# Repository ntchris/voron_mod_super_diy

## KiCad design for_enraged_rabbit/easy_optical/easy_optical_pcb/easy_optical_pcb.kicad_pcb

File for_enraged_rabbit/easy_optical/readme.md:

# ERCF Easy Optical Encoder Module
For ERCF: to make it easier for everyone to use a transmissive optical sensor

in one simple sentence, a DIY friendly, a much cheaper and easier blinky sensor module for ERCF.

## What is this:

for ERCF (Enraged Rabbit Carrot Feeder Multiple Material System for Voron or alike 3D printers)
replace the original reflective optical sensor which is quite not reliable.
so mneuhaus made a transmissive optical sensor encoder called Binky, which should provide a much more reliable encoder functions/counter.
 https://github.com/mneuhaus/EnragedRabbitProject/tree/main/usermods/Binky
 
* What is a transmissive optical sensor
an optical sensor, or photo sensor, slot type, like SX1103, or ITR9608.
It has a infrared diode and a receiver, if an object blocks the infrared light, the receiver detects it and triggers/send a signal.

However, there are still some problems remains with Binky module, 
* blinky PCB is quite expensive, plus shipping (international!) and tax, I'm afraid we are looking at ~~30$ or more. 
* Also the PCB is quite difficult to make via DIY methods. 
* And some components, in my opinion, is too expensive or useless.
So I made this Easy Optical module for ERCF.
The goal is to save a ton of money not to buy binky PCB or wait for shipping, or buy some expensive and /or unncessary components. 
and we can make it using some easy home DIY methods, CNC milling or chemical etching.

## Easy Optical PCB module feature list:
* single side PCB design, reduce PCB DIY complicity
* 0.5mm thick traces and large clearance, good precision/error tolerance, so we can easily make it at home with a cheap CNC or chemical method. I made mine using a DIY CNC made by myself.
* Use a much cheaper slotted optical sensor - ITR20403, it's small enough and very cheap, about 2$ for 10pcs. 
https://everlighteurope.com/index.php?controller=attachment?id_attachment=5394 comparing with the SX1103, it's about 1$ each.
* removed a useless component small inverter, to reduce cost and efforts for making the pcb/soldering.
* using a 3mm through hole LED, it fits the rabbit eyes much better and brighter.
* Kicad 7 is used to create the schematics and PCB. full schematics/PCB project/source are provided

## Things to pay attention while making the PCB at home.
* Only front side of the PCB is needed, back side is not needed, just optional.
* for single side PCB, the 3pins connector must be soldered on the front side of the PCB, because the back side has no copper. 
* For single side PCB, the 3pins connect drill hole better be 0.8mm, so it's tight enough. If the holes are too large, the pin will be easily pulled out since the copper is not strong enough to hold it against some large pull up force.
* If don't care about flashing rabbit eyes, some components are not needed, so to make it even easier to make: R3 (D1 3mm LED, R3 1k)for LED, Q1 ( AO3402 Nchannel Mosfet), C2 (10u)
* when installing the ITR20403, the 45 degree edge is facing outside of PCB, longer pin is facing 3mm led. there are two plastic mounting pin under it, one is larger, it's closer to the 3mm led. hold it tight and close on the PCB when solder.

## Component list
* C1	1	1u	C      0805 SMD Capacitor, filtering signal.
* C2	1	10u	C      0805 SMD Capacitor, optional
* D1	1	LED	LED    3mm red LED, A on right, K on left. optional
* H1	1	MountingHole	2mm mounting hole.
* J1	1	Conn_01x03	Conn_01x03,  
* Q1	1	AO3402_N_Mosfet	, Nchannel mosfet, for red LED only, optional.
* R1    1   1K  R   0805 SMD Resistor,  for optical sensor infrared
* R3	1	1k	R   0805 SMD Resistor    Optional
* R2	1	10k	R      0805 SMD Resistor , pull up for optical sensor
* R4	1	0	R     1206 0R resistor, act as a jumper wire, if don't have it, just fly a wire.
* U1	1	ITR20403  optical sensor

## Operation theory

It couldn't be simpler and easier than this.
* When the ITR20403 sensor is power on, R1 (1K) resistor make 5V power supply to provide and reduce a suitable current for the sensor's infrared led, about (5-2)/1k = ~~3ma.
* When nothing blocking, the infrared light fire on the other side collector/emitter, so it's kind of connected, so our signal termial has about 0V, low.
* When our 3D printed gear blocking the infrared, the E/C is disconnected, so the signal point is pull high.
So our easy optical module can send low/high signal as the gear rotates, and it's super reliable, since the gear can always block the light and let the light pass.

* Optional for blinking rabbit eyes.
 N channel mosfet gate when pull high, it power on the 3mm LED.

( low or high doesn't matter in our application, as long as it can be triggered and change, it's good enough. also this is not a high speed application. )

## Encoder 3DPrint part 
The 3D pirnted part is modified based on binky's encoder however made quite a few changes as below:

### modification list:

1. larger cut for optical sensor, so it fits IT20403  ( 7mm for sensor 6.4mm width, 4.7mm for 4.2mm length.), it's slightly larger than the sx1103 (in binky pcb), but much much cheaper than SX1103. ITR20403 is only a bit wider than it (6.4mm VS 5mm).
1. larger LED hole so it fits for through hole 3mm led, and the led's bottom is even larger ( I think it's the smallest through hole cheap led in the market)
1. very very slightly larger (0.02mm) slot wheel, and tighter fit on bondtech gear. So it won't easily move on the bondtech gear. also it can block the light better.
1. 0.2mm lower pcb mount position so to let slot wheel fit deeper/better in the optical sensor
1. larger gap in the brake, so it doesn't get stuck with main body
1. thicker gear slot wheel (1.2mm now), so it can block light better.
  I don't think color matters, as long as it's not translucent. (I used grey color to print that on purpose to prove that. )

## Installation
* follow original ERCF's guide page 49, need 3 heat inserts, one bearing 623, a few 20mm M3 screws, 2 magnets 3x6mm
* it's better to make a new working encoder module first, and not to destroy the existing/working encoder, if you already have one running well, and if you have all the necessary parts, especially the bondtech gear...
* check 3 pins connector polaries before connect,  G V S, first one is Gnd, middle one is 5V, Sigal at right most. 
* modify ercf.py file ( in PI /home/yourname/ERCF-Software-V3/extras , about line 139 DEFAULT_ENCODER_RESOLUTION = 1.0   , as stated in binky's readme
* put the 3mm red led into the 3d printed part hole.
* use a 2mm screw to mount the PCB.
* add some suitable oil inside the bondtech gear idler.

## check again ercf is restored in proper working state after new encoder installation,  check points and potential problems are:  
* 2 X latches are locked again
* servo can move do up and down correctly, if it cannot move down correctly, it cannot push the bondtech gear to hold the filament tight, so filament cannot move correctly, making sensor cannot detect movement.
* selector can move freely. turn motor off ( ercf_motors_off), move selector by hand to feel if there is any resistance, if so, use a file tool to fix it.
* some filament can be grinded and wear out so bondtech gear cannot catch it well, observe, see if filament are actually moving out and in to the correct distance when running the calibrate command, we can easily tell if this problem happens. (It happened to my ABS, too soft and easily grinded out)

## Testing
* insert a filament in encoder, while pulling it in and out, check rabbit eyes are blinking , (only if all optional LED components are installed /soldered)
* use gcode command ERCF_CALIBRATE_ENCODER for a few times, it should always have a result of 2.0#, it shouldn't be too much difference than 2.0 something. If not, need to investigate.

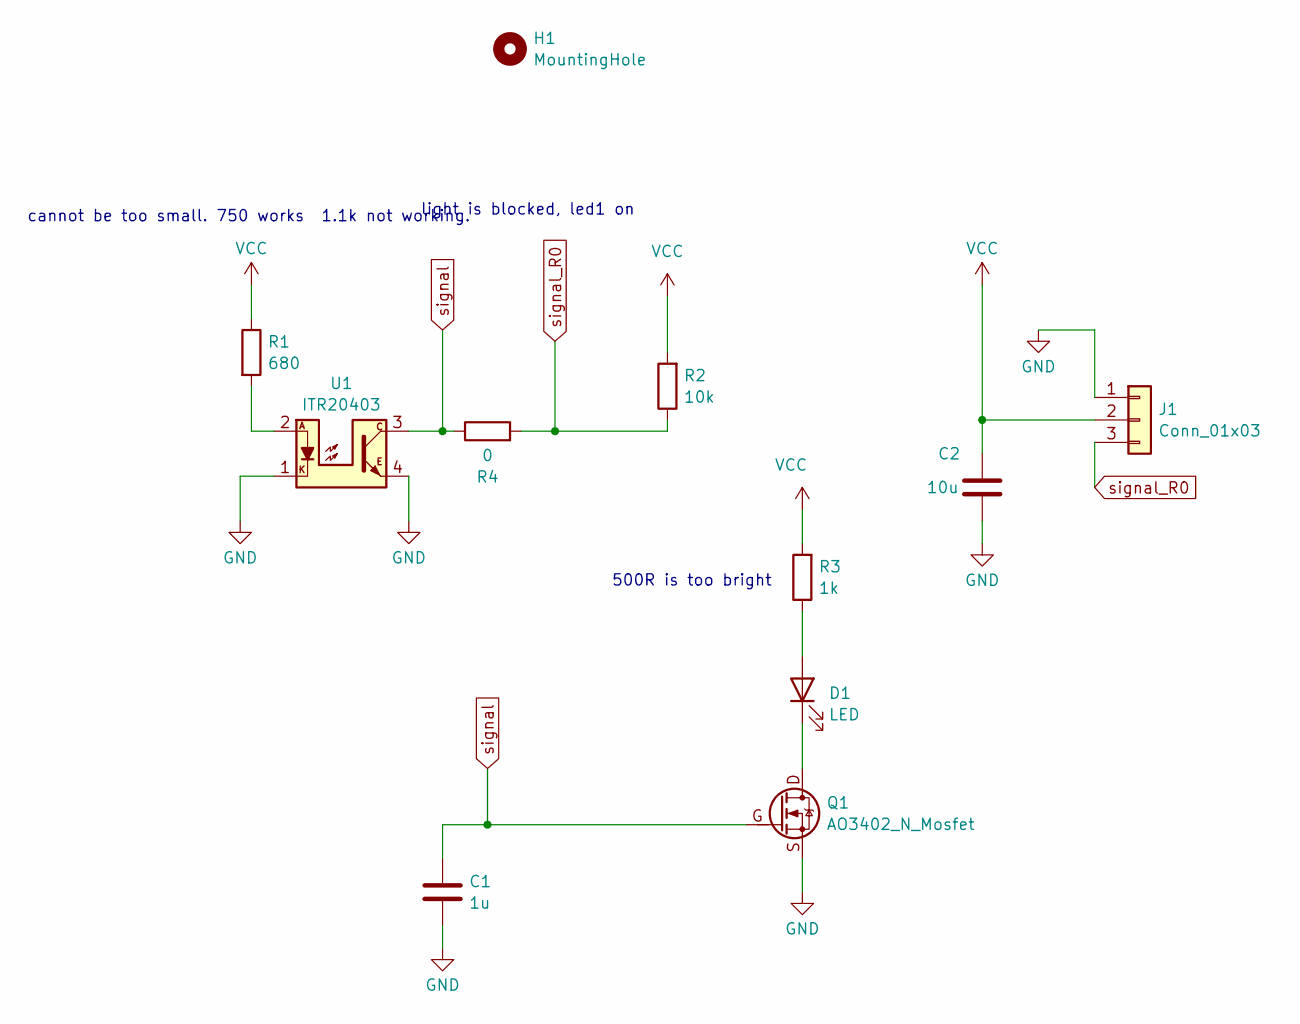
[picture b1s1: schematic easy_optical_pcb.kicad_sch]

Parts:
C1: 1u; C_0805_2012Metric_Pad1.20x1.50mm_HandSolder
C2: 10u; C_0805_2012Metric_Pad1.20x1.50mm_HandSolder
D1: LED; LED_D3.0mm
H1: MountingHole; MountingHole_2.1mm
J1: Conn_01x03; PinHeader_1x03_P2.54mm_Vertical
Q1: AO3402_N_Mosfet; SOT-23_PMOSFET
R1: 680; R_0805_2012Metric_Pad1.20x1.50mm_HandSolder
R2: 10k; R_0805_2012Metric_Pad1.20x1.50mm_HandSolder
R3: 1k; R_0805_2012Metric_Pad1.20x1.50mm_HandSolder
R4: 0; R_1206_3216Metric_Pad1.33x1.80mm_HandSolder
U1: ITR20403; Optical_ITR20403

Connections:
GND: C1.2, C2.2, J1.1, Q1.S, U1.1, U1.4
unnamed: D1.A, R3.1
unnamed: D1.K, Q1.D
unnamed: R1.2, U1.2
VCC: C2.1, J1.2, R1.1, R2.2, R3.2
signal: C1.1, Q1.G, R4.1, U1.3
signal_R0: J1.3, R2.1, R4.2

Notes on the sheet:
cannot be too small. 750 works 1.1k not working.
light is blocked, led1 on
500R is too bright

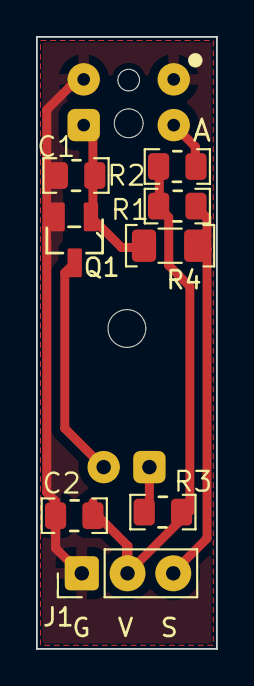
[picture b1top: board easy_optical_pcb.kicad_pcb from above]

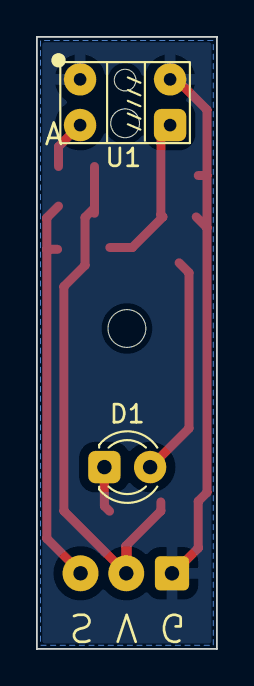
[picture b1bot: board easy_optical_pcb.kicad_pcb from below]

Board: 2 copper layers, 10.0 x 34.0 mm, 11 parts (2 on the bottom side), 7 nets.

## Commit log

2023-09-17 continue to init
    continue to init
2023-09-17 add ercf klipper config
2023-09-17 add uart jumper picture
    add uart jumper picture
2023-09-17 added readme
2023-09-17 added a few more config file for ERCF
2023-09-18 add always enable ERCF in readme
2023-09-18 adding mellow picture
2023-09-18 readme typo fix
2023-09-18 more fixing typo
2023-09-18 more fix
2023-09-19 more notes and pin diagram
2023-09-19 more notes
2023-09-19 more notes!
2023-09-22 add description for time too close error
    add description for time too close error
2023-10-22 added BTT ERCF
2023-10-22 add pictures
2023-10-22 fix motor pin photo
    fix motor pin photo
2023-10-22 add a new line
    add a new line
2023-10-22 rename so it can show automatically
2023-10-22 remove btt template config file
2023-10-22 add more test steps
2023-10-31 adding ERCF easy optical project
2023-10-31 modify readme
    shrink pictures
2023-10-31 shrink even more
2023-10-31 move pcb step file to the CAD folder
2023-10-31 update the project name and desc
2023-11-03 add more trouble shooting for ercf move delta
2024-07-20 add more projects
2024-07-21 add gear box black mod for 80T cnc metal pulley
2024-08-10 add ercf v2 selector power drive pulley 60T and 20T driving system
    add ercf v2 selector power drive pulley 60T and 20T driving system
2024-08-10 rename folder to power drive selector 60T pulley
    rename folder to power drive selector 60T pulley
2024-08-10 add more picture
2024-08-10 more picture
2024-08-10 add front view pictures and screw pictures
2024-08-10 added stepper motor screw warning
2024-08-10 remove finger from picture
2024-08-10 add video
2024-08-11 rotate stl file to the correct print orientation
2024-08-11 to let ERCF V2 support larger 28mm servo
    to let ERCF V2 support larger 28mm servo
2024-08-11 write readme
2024-08-11 add more picture and add readme
2024-08-11 add overview picture
2024-08-11 fix readme
2024-08-11 add selector body bottom view
2024-08-11 add a new view picture
2024-08-27 add filament tension sensor module
2024-08-27 fix readme file
2024-09-14 add 28mm servo selector Version2
2024-09-14 update power selector drive f3z file
2024-09-14 update servo arm stl orientation for print
2024-09-14 add ercf cutter beta7 mod
2024-09-14 ercf cutter add cad file and change description
2024-09-14 add f3d file
2024-09-14 update stl orientation
2024-09-14 add picture
2024-09-14 update readme for software config change
2025-02-14 add motor buffer samla project source code and doc
